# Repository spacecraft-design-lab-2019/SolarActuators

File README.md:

# SolarActuators
Team 3 Repository

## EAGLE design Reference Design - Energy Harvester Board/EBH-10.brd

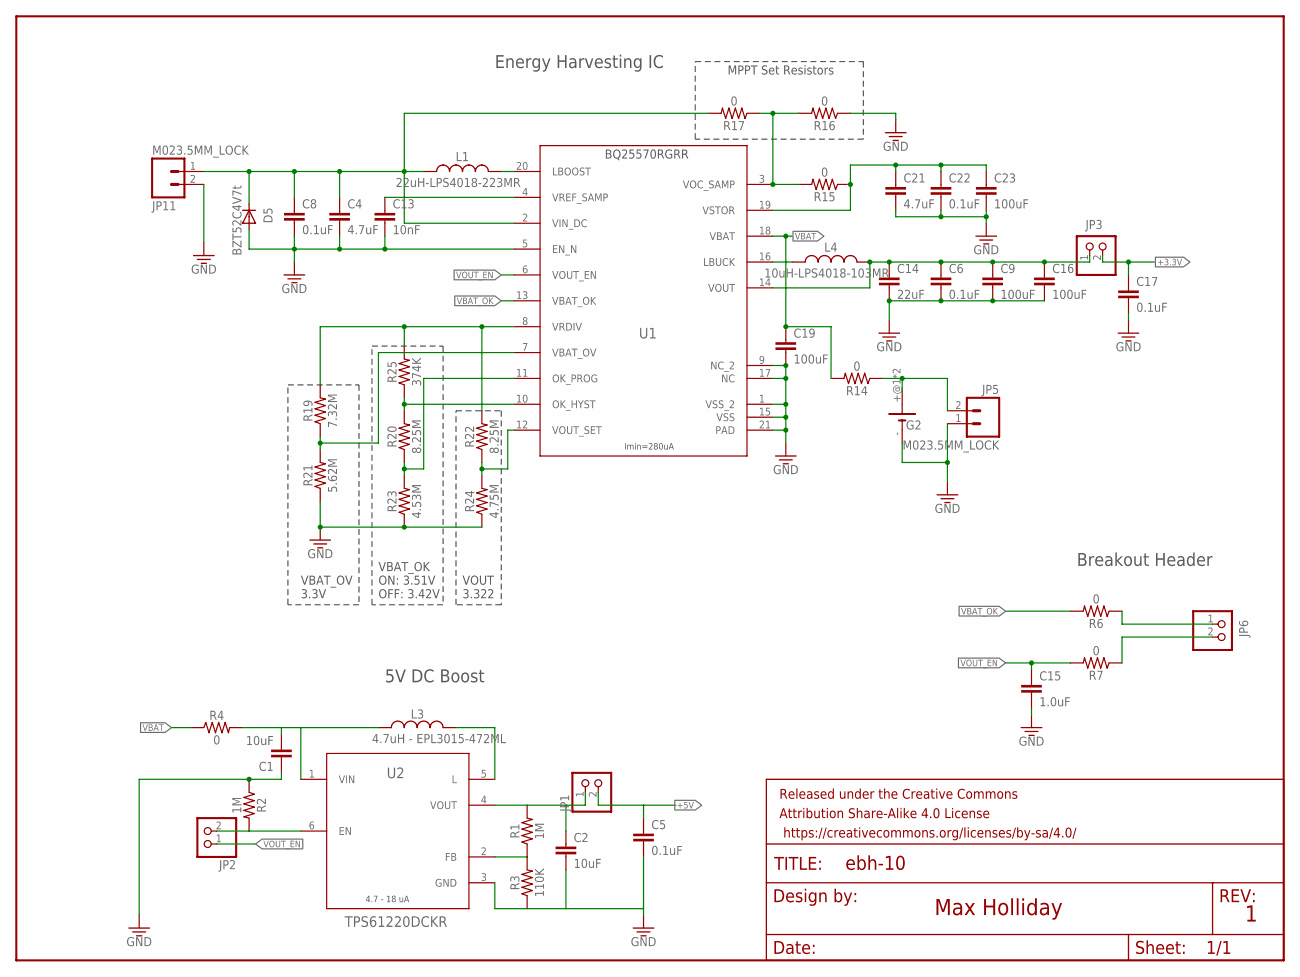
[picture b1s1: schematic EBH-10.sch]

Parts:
C1, C2: 10uF; 0603
C4, C21: 4.7uF; 0603
C5, C6, C8, C17, C22: 0.1uF; 0603
C9, C16, C19, C23: 100uF; 0603
C13: 10nF; 0603
C14: 22uF; 0805
C15: 1.0uF; 0603
D5: BZT52C4V7t; SOD523
FRAME1: FRAME-LETTERNO_PACKAGE; DUMMY
G2: 10MM_SM_COIN_CELL_CLIP
JP1, JP2, JP3, JP6: PINHD-1X2; 1X02
JP5, JP11: M023.5MM_LOCK; SCREWTERMINAL-3.5MM-2_LOCK
L1: 22uH-LPS4018-223MR; LPS4018
L3: 4.7uH - EPL3015-472ML; DFE322512C
L4: 10uH-LPS4018-103MR; LPS4018
R1, R2: 1M; 0603
R3: 110K; 0603
R4, R6, R7, R14, R15, R16, R17: 0; 0603
R19: 7.32M; 0603
R20, R22: 8.25M; 0603
R21: 5.62M; 0603
R23: 4.53M; 0603
R24: 4.75M; 0603
R25: 374K; 0603
U1: Value; RGR0020A
U2: TPS61220DCKR; DCK0006A

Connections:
+3.3V: C17.1, JP3.2
+5V: C5.1, JP1.2
GND: C1.1, C2.2, C4.2, C5.2, C6.2, C8.2, C9.2, C13.2, C14.2, C15.2, C16.2, C17.2, C19.2, C21.2, C22.2, C23.2, D5.A, G2.-, JP5.1, JP11.2, R2.1, R3.1, R16.1, R21.1, R23.1, R24.1, U1.1 (VSS_2), U1.5 (EN_N), U1.9 (NC_2), U1.15 (VSS), U1.17 (NC), U1.21 (PAD), U2.3 (GND)
unnamed: R1.1, R3.2, U2.2 (FB)
unnamed: C2.1, JP1.1, R1.2, U2.4 (VOUT)
unnamed: L3.P$2 (2), U2.5 (L)
unnamed: C1.2, L3.P$1 (1), R4.2, U2.1 (VIN)
unnamed: JP2.2, R2.2, U2.6 (EN)
unnamed: C6.1, C9.1, C14.1, C16.1, JP3.1, L4.2, U1.14 (VOUT)
unnamed: L4.1, U1.16 (LBUCK)
unnamed: R15.2, R16.2, R17.1, U1.3 (VOC_SAMP)
unnamed: G2.+@1 (+), G2.+@2 (+), JP5.2, R14.1
unnamed: C13.1, U1.4 (VREF_SAMP)
unnamed: C21.1, C22.1, C23.1, R15.1, U1.19 (VSTOR)
unnamed: JP6.1, R6.1
unnamed: JP6.2, R7.1
unnamed: L1.2, U1.20 (LBOOST)
unnamed: C4.1, C8.1, D5.C, JP11.1, L1.1, R17.2, U1.2 (VIN_DC)
unnamed: R19.1, R21.2, U1.7 (VBAT_OV)
unnamed: R22.1, R24.2, U1.12 (VOUT_SET)
unnamed: R20.2, R25.1, U1.10 (OK_HYST)
unnamed: R20.1, R23.2, U1.11 (OK_PROG)
unnamed: R19.2, R22.2, R25.2, U1.8 (VRDIV)
VBAT: C19.1, R4.1, R14.2, U1.18 (VBAT)
VBAT_OK: R6.2, U1.13 (VBAT_OK)
VOUT_EN: C15.1, JP2.1, R7.2, U1.6 (VOUT_EN)

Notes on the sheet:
VOUT 3.322
VBAT_OK ON: 3.51V OFF: 3.42V
VBAT_OV 3.3V
4.7 - 18 uA
Imin=280uA
MPPT Set Resistors
BQ25570RGRR
Max Holliday
5V DC Boost
Energy Harvesting IC
Breakout Header

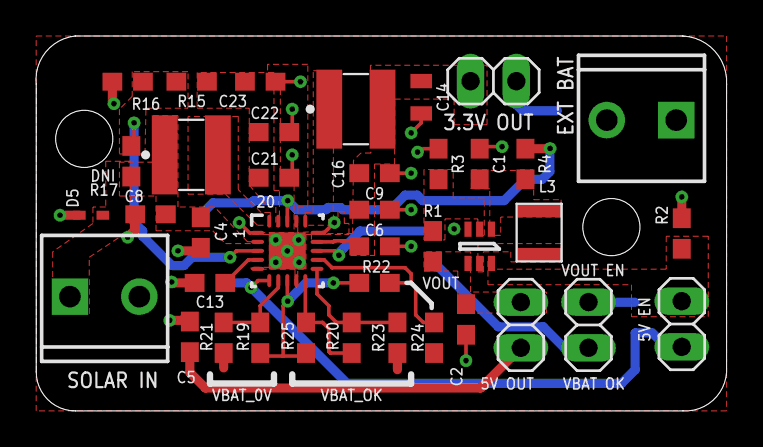
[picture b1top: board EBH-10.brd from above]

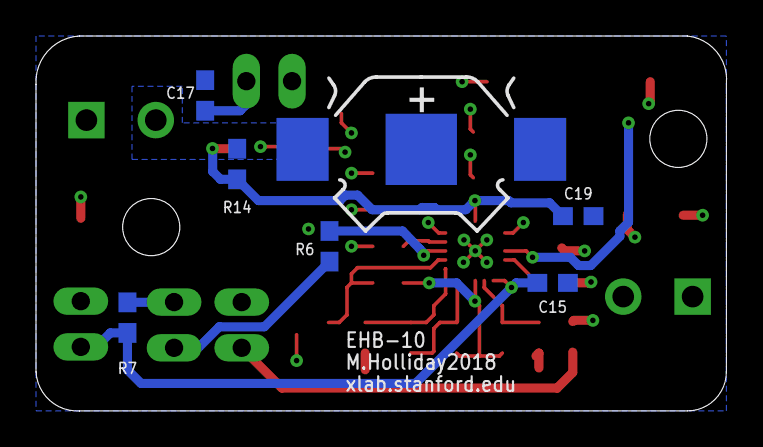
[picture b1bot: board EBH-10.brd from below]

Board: 2 copper layers, 38.4 x 20.8 mm, 47 parts (7 on the bottom side), 26 nets.

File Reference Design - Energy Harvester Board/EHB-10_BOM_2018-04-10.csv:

Part,Value,Device,Package,Description,ALTERNATEPARTNUMBER,APPLICATION_BUILDNUMBER,COMPTYPE,DESIGNER,MANUFACTURER,MOUNTTYPE,PACKAGEREFERENCE,PARTNUMBER,PIN_COUNT,PROD_ID,REFDES,ROHS,TYPE,VALUE,VERSION
C1,10uF,10UF-0603-6.3V-20%,603,10.0µF ceramic capacitors,,,,,,,,,,CAP-11015,,,,10uF,
C2,10uF,10UF-0603-6.3V-20%,603,10.0µF ceramic capacitors,,,,,,,,,,CAP-11015,,,,10uF,
C4,4.7uF,4.7UF0603,603,4.7µF ceramic capacitors,,,,,,,,,,CAP-08280,,,,4.7uF,
C5,0.1uF,0.1UF-0603-25V-(+80/-20%),603,0.1µF ceramic capacitors,,,,,,,,,,CAP-00810,,,,0.1uF,
C6,0.1uF,0.1UF-0603-25V-(+80/-20%),603,0.1µF ceramic capacitors,,,,,,,,,,CAP-00810,,,,0.1uF,
C8,0.1uF,0.1UF-0603-25V-(+80/-20%),603,0.1µF ceramic capacitors,,,,,,,,,,CAP-00810,,,,0.1uF,
C9,100uF,0.1UF-0603-25V-(+80/-20%),603,0.1µF ceramic capacitors,,,,,,,,,,CAP-00810,,,,0.1uF,
C13,10nF,10NF-0603-50V-10%,603,0.01uF/10nF/10,,,,,,,,,,,,,,,
C14,22uF,22UF-0805-6.3V-20%,805,22µF ceramic capacitors,,,,,,,,,,CAP-08402,,,,22uF,
C15,1.0uF,1.0UF-0603-16V-10%,603,1µF ceramic capacitors,,,,,,,,,,CAP-00868,,,,1.0uF,
C16,100uF,0.1UF-0603-25V-(+80/-20%),603,0.1µF ceramic capacitors,,,,,,,,,,CAP-00810,,,,0.1uF,
C17,0.1uF,0.1UF-0603-25V-(+80/-20%),603,0.1µF ceramic capacitors,,,,,,,,,,CAP-00810,,,,0.1uF,
C19,100uF,0.1UF-0603-25V-(+80/-20%),603,0.1µF ceramic capacitors,,,,,,,,,,CAP-00810,,,,0.1uF,
C21,4.7uF,4.7UF0603,603,4.7µF ceramic capacitors,,,,,,,,,,CAP-08280,,,,4.7uF,
C22,0.1uF,0.1UF-0603-25V-(+80/-20%),603,0.1µF ceramic capacitors,,,,,,,,,,CAP-00810,,,,0.1uF,
C23,100uF,0.1UF-0603-25V-(+80/-20%),603,0.1µF ceramic capacitors,,,,,,,,,,CAP-00810,,,,0.1uF,
D5,BZT52C4V7t,DIODE-SOD523,SOD523,DIODE,,,,,,,,,,,,,,,
FRAME1,FRAME-LETTERNO_PACKAGE,FRAME-LETTERNO_PACKAGE,DUMMY,Schematic Frame - Letter,,,,Nobody,,,,,,,,,,,v01
G2,10MM_SM_COIN_CELL_CLIP,10MM_SM_COIN_CELL_CLIP,10MM_SM_COIN_CELL_CLIP,Battery cell clip for CR927,,,,,,,,,,,,,,,
JP1,,PINHD-1X2,1X02,PIN HEADER,,,,,,,,,,,,,,,
JP2,,PINHD-1X2,1X02,PIN HEADER,,,,,,,,,,,,,,,
JP3,,PINHD-1X2,1X02,PIN HEADER,,,,,,,,,,,,,,,
JP5,M023.5MM_LOCK,M023.5MM_LOCK,SCREWTERMINAL-3.5MM-2_LOCK,"Standard 2-pin 0.1 header. Use with""",,,,,,,,,,CONN-08399,,,,,
JP6,,PINHD-1X2,1X02,PIN HEADER,,,,,,,,,,,,,,,
JP11,M023.5MM_LOCK,M023.5MM_LOCK,SCREWTERMINAL-3.5MM-2_LOCK,"Standard 2-pin 0.1 header. Use with""",,,,,,,,,,CONN-08399,,,,,
L1,22uH-LPS4018-223MR,COILCRAFT-LPS4018,LPS4018,Coilcraft,,,,,,,,,,,,,,,
L3,4.7uH - EPL3015-472ML,INDUCTORDFE322512C,DFE322512C,A very specific inductor,,,,,,,,,,,,,,,
L4,10uH-LPS4018-103MR,COILCRAFT-LPS4018,LPS4018,Coilcraft,,,,,,,,,,,,,,,
R1,1M,1MOHM-0603-1/4W-5%,603,1MO resistor,,,,,,,,,,RES-07868,,,,1M,
R2,1M,1MOHM-0603-1/4W-5%,603,1MO resistor,,,,,,,,,,RES-07868,,,,1M,
R3,110K,100KOHM-0603-1/10W-1%,603,100kO resistor,,,,,,,,,,RES-07828,,,,100k,
R4,0,0OHM-0603-1/10W-5%,603,0O resistor,,,,,,,,,,RES-08609,,,,0,
R6,0,0OHM-0603-1/10W-5%,603,0O resistor,,,,,,,,,,RES-08609,,,,0,
R7,0,0OHM-0603-1/10W-5%,603,0O resistor,,,,,,,,,,RES-08609,,,,0,
R14,0,0OHM-0603-1/10W-5%,603,0O resistor,,,,,,,,,,RES-08609,,,,0,
R15,0,0OHM-0603-1/10W-5%,603,0O resistor,,,,,,,,,,RES-08609,,,,0,
R16,0,0OHM-0603-1/10W-5%,603,0O resistor,,,,,,,,,,RES-08609,,,,0,
R17,0,0OHM-0603-1/10W-5%,603,0O resistor,,,,,,,,,,RES-08609,,,,0,
R19,7.32M,1MOHM-0603-1/4W-5%,603,1MO resistor,,,,,,,,,,RES-07868,,,,1M,
R20,8.25M,1MOHM-0603-1/4W-5%,603,1MO resistor,,,,,,,,,,RES-07868,,,,1M,
R21,5.62M,1MOHM-0603-1/4W-5%,603,1MO resistor,,,,,,,,,,RES-07868,,,,1M,
R22,8.25M,1MOHM-0603-1/4W-5%,603,1MO resistor,,,,,,,,,,RES-07868,,,,1M,
R23,4.53M,1MOHM-0603-1/4W-5%,603,1MO resistor,,,,,,,,,,RES-07868,,,,1M,
R24,4.75M,1MOHM-0603-1/4W-5%,603,1MO resistor,,,,,,,,,,RES-07868,,,,1M,
R25,374K,1MOHM-0603-1/4W-5%,603,1MO resistor,,,,,,,,,,RES-07868,,,,1M,
U1,Value,BQ25570RGRR,RGR0020A,,BQ25570RGRT,*,IC,,Texas Instruments,SMT,RGR0020A,BQ25570RGRR,21,,RefDes,Y,TYPE,Value,
U2,TPS61220DCKR,TPS61220DCKR,DCK0006A,,,,IC,,Texas Instruments,SMT,DCK0006A,TPS61220DCK,6,,RefDes,Y,TYPE,Value,

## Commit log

2019-10-08 Create Charging circuit reference
2019-10-08 Added datasheet for charging IC
2019-10-09 Example solar cell & torquer designs from PandaSat
2019-10-10 Added power over orbit calculator
2019-10-11 adding bq25570 example design and datasheet
2019-10-13 Added magnetorquer references
2019-10-14 Added blank files for the new PCB layout
2019-10-14 Added components + lib to board!
2019-10-21 Set up directory for antenna/+Z board.
2019-10-21 Added sub-files, did early layout and cleanup.
2019-10-21 Preliminary layout, pending updates from AV about radio.
2019-10-24 add referece document for parallel operation.
2019-10-28 PCB test log file added
2019-10-30 Added energy circuit test notes
2019-10-31 Added updates power over orbit calculations
2019-11-12 Update test report for diode lamp_light
2019-11-12 Created main.py for burn wire testing
    Save this to a trinket M0 and play with the duty_cycle variable to find the optimal duty cycle for safe burning
2019-11-12 New testing report added
2019-12-09 Reference document for energy harvest board testing is added.
2019-12-09 Voltage plot is added.
2019-12-09 Add Vin < Vout(i.e., EXT BAT) testing voltage plot
2019-12-12 Detailed energy harvest board testing report

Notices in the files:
parts and their libraries:
SparkFun-Capacitors: Licensing: Creative Commons ShareAlike 4.0 International - https://creativecommons.org/licenses/by-sa/4.0
SparkFun-Aesthetics: Released under the Creative Commons Attribution Share-Alike 4.0 License
SparkFun-Aesthetics: https://creativecommons.org/licenses/by-sa/4.0
